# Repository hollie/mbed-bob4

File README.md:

mbed-bob4
=========

Basic breakout board for mbed (ethernet, USB, current sensor, GPIO)

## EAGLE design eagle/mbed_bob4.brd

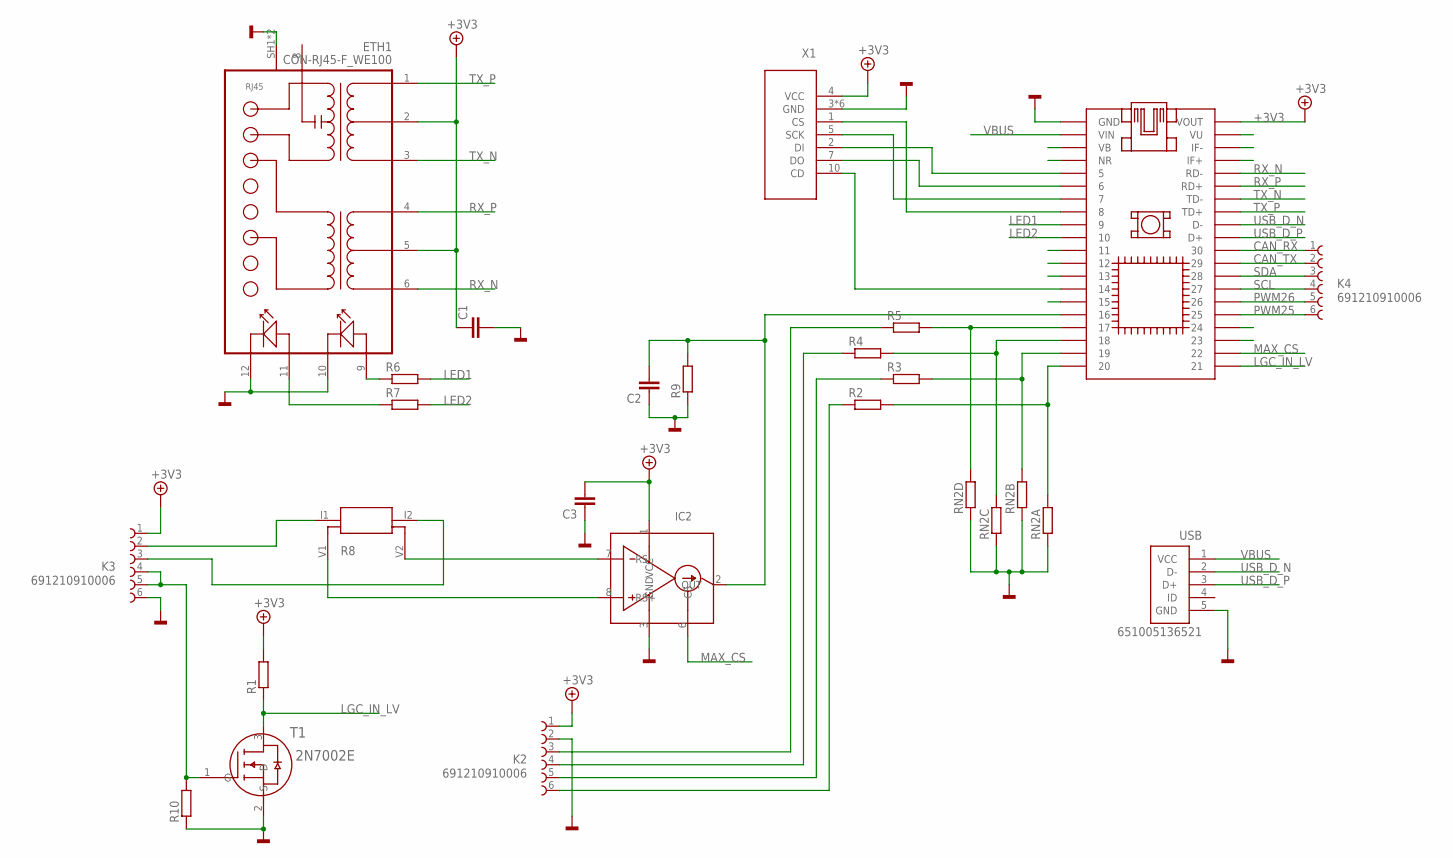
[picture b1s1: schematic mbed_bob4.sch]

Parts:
C1, C2, C3: C0805_RFLW; 0805_RFLW
ETH1: CON-RJ45-F_WE100; 74990111215A
IC1: MBED-SOCKET
IC2: MAX9934; UMAX8
K2, K3, K4: 691210910006
R1, R2, R3, R4, R5, R6, R7, R9, R10: R0805_RFLW; 0805_RFLW
R8: R_KELVIN; R_KELVIN_1206
RN2: RESISTOR_ARRAY_4TC164; RN_TC164
T1: 2N7002E; SOT23-3L
USB: 651005136521
X1: SDCARDSHORT; SD_SHORT

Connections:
+3V3: C1.P$3 (1), C3.P$4 (2), ETH1.2 (CTD), ETH1.5 (CRD), IC1.VOUT, IC1.VOUTA (VOUT), IC2.1 (VCC), K2.1, K3.1, R1.P$4 (2), X1.4 (VCC)
CAN_RX: IC1.30, IC1.30A (30), K4.1
CAN_TX: IC1.29, IC1.29A (29), K4.2
GND: C1.P$4 (2), C2.P$3 (1), C3.P$3 (1), ETH1.10 (YELLOW_CATHODE), ETH1.12 (GREEN_CATHODE), ETH1.SH1 (SHIELD), ETH1.SH2 (SHIELD), IC1.GND, IC1.GNDA (GND), IC2.3 (GND), K2.2, K3.6, R9.P$3 (1), R10.P$3 (1), RN2.1, RN2.2 (1), RN2.3 (1), RN2.4 (1), T1.2 (S), USB.5 (GND), X1.3 (GND), X1.6 (GND), X1.GND@1 (GND), X1.GND@2 (GND), X1.GND@3 (GND), X1.GND@4 (GND)
LED1: IC1.9, IC1.9A (9), R6.P$4 (2)
LED2: IC1.10, IC1.10A (10), R7.P$4 (2)
LGC_IN_LV: IC1.21, IC1.21A (21), R1.P$3 (1), T1.3 (D)
MAX_CS: IC1.22, IC1.22A (22), IC2.6 (CS)
unnamed: IC1.17, IC1.17A (17), R5.P$4 (2), RN2.5 (2)
unnamed: IC1.14, IC1.14A (14), X1.10 (CD)
unnamed: K2.6, R2.P$3 (1)
unnamed: IC1.20, IC1.20A (20), R2.P$4 (2), RN2.8 (2)
unnamed: IC1.19, IC1.19A (19), R3.P$4 (2), RN2.7 (2)
unnamed: IC1.18, IC1.18A (18), R4.P$4 (2), RN2.6 (2)
unnamed: K2.5, R3.P$3 (1)
unnamed: K2.4, R4.P$3 (1)
unnamed: K2.3, R5.P$3 (1)
unnamed: ETH1.11 (GREEN_ANODE), R7.P$3 (1)
unnamed: ETH1.9 (YELLOW_ANODE), R6.P$3 (1)
unnamed: K3.4, K3.5, R10.P$4 (2), T1.1 (G)
unnamed: IC1.7, IC1.7A (7), X1.5 (SCK)
unnamed: IC1.8, IC1.8A (8), X1.1 (CS)
unnamed: IC1.5, IC1.5A (5), X1.2 (DI)
unnamed: IC1.6, IC1.6A (6), X1.7 (DO)
unnamed: IC1.VB, IC1.VBA (VB)
unnamed: IC1.NR, IC1.NRA (NR)
unnamed: IC1.11, IC1.11A (11)
unnamed: IC1.12, IC1.12A (12)
unnamed: IC1.13, IC1.13A (13)
unnamed: IC1.15, IC1.15A (15)
unnamed: C2.P$4 (2), IC1.16, IC1.16A (16), IC2.2 (OUT), R9.P$4 (2)
unnamed: K3.2, R8.I1
unnamed: IC1.23, IC1.23A (23)
unnamed: IC1.24, IC1.24A (24)
unnamed: IC1.IF+, IC1.IF+A (IF+)
unnamed: IC1.IF-, IC1.IF-A (IF-)
unnamed: IC1.VU, IC1.VUA (VU)
unnamed: IC2.7 (RS-), R8.V2
unnamed: IC2.8 (RS+), R8.V1
unnamed: K3.3, R8.I2
PWM25: IC1.25, IC1.25A (25), K4.6
PWM26: IC1.26, IC1.26A (26), K4.5
RX_N: ETH1.6 (RD-), IC1.RD-, IC1.RD-A (RD-)
RX_P: ETH1.4 (RD+), IC1.RD+, IC1.RD+A (RD+)
SCL: IC1.27, IC1.27A (27), K4.4
SDA: IC1.28, IC1.28A (28), K4.3
TX_N: ETH1.3 (TD-), IC1.TD-, IC1.TD-A (TD-)
TX_P: ETH1.1 (TD+), IC1.TD+, IC1.TD+A (TD+)
USB_D_N: IC1.D-, IC1.D-A (D-), USB.2 (D-)
USB_D_P: IC1.D+, IC1.D+A (D+), USB.3 (D+)
VBUS: IC1.VIN, IC1.VINA (VIN), USB.1 (VCC)

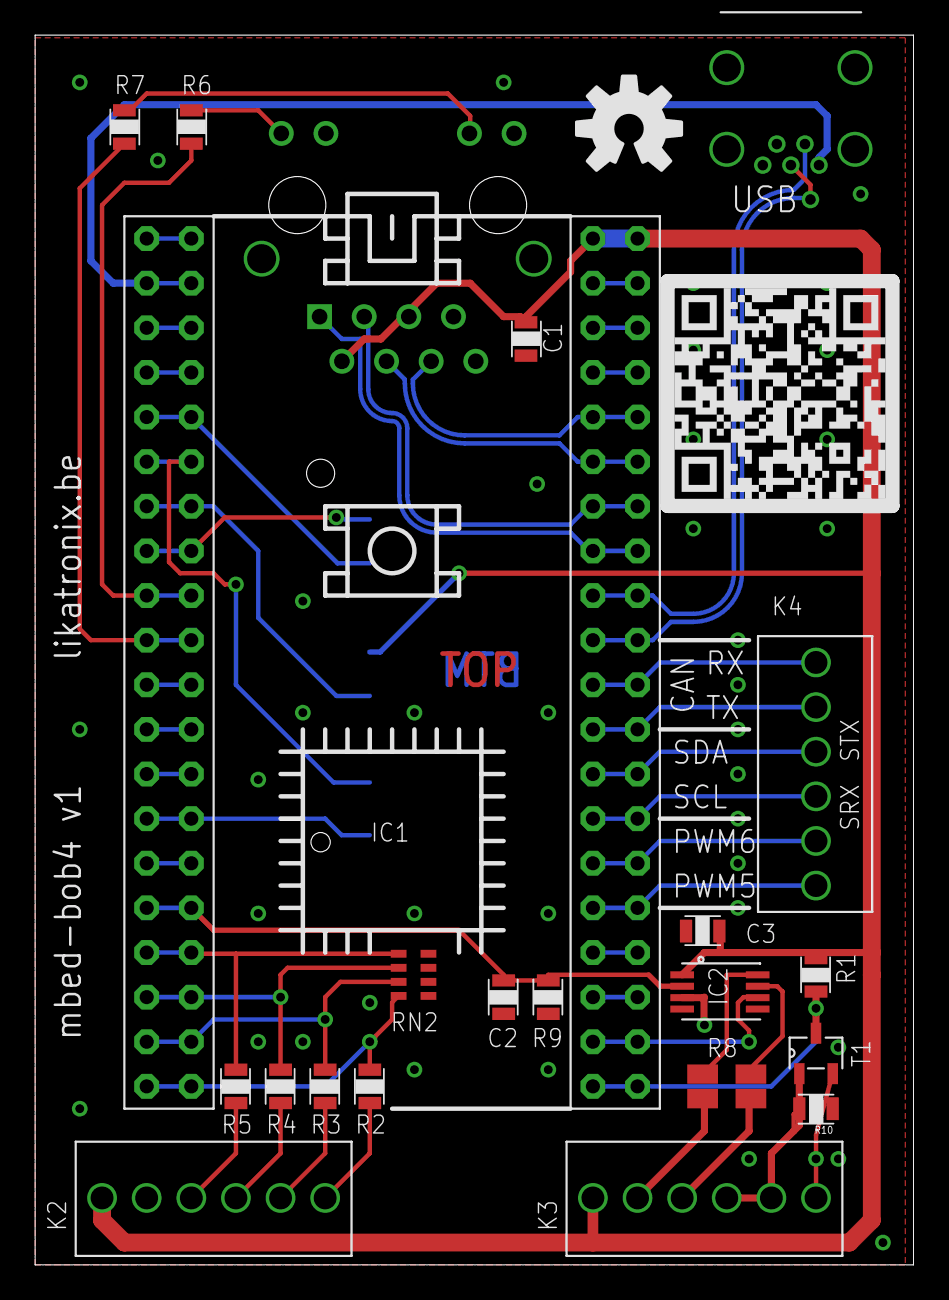
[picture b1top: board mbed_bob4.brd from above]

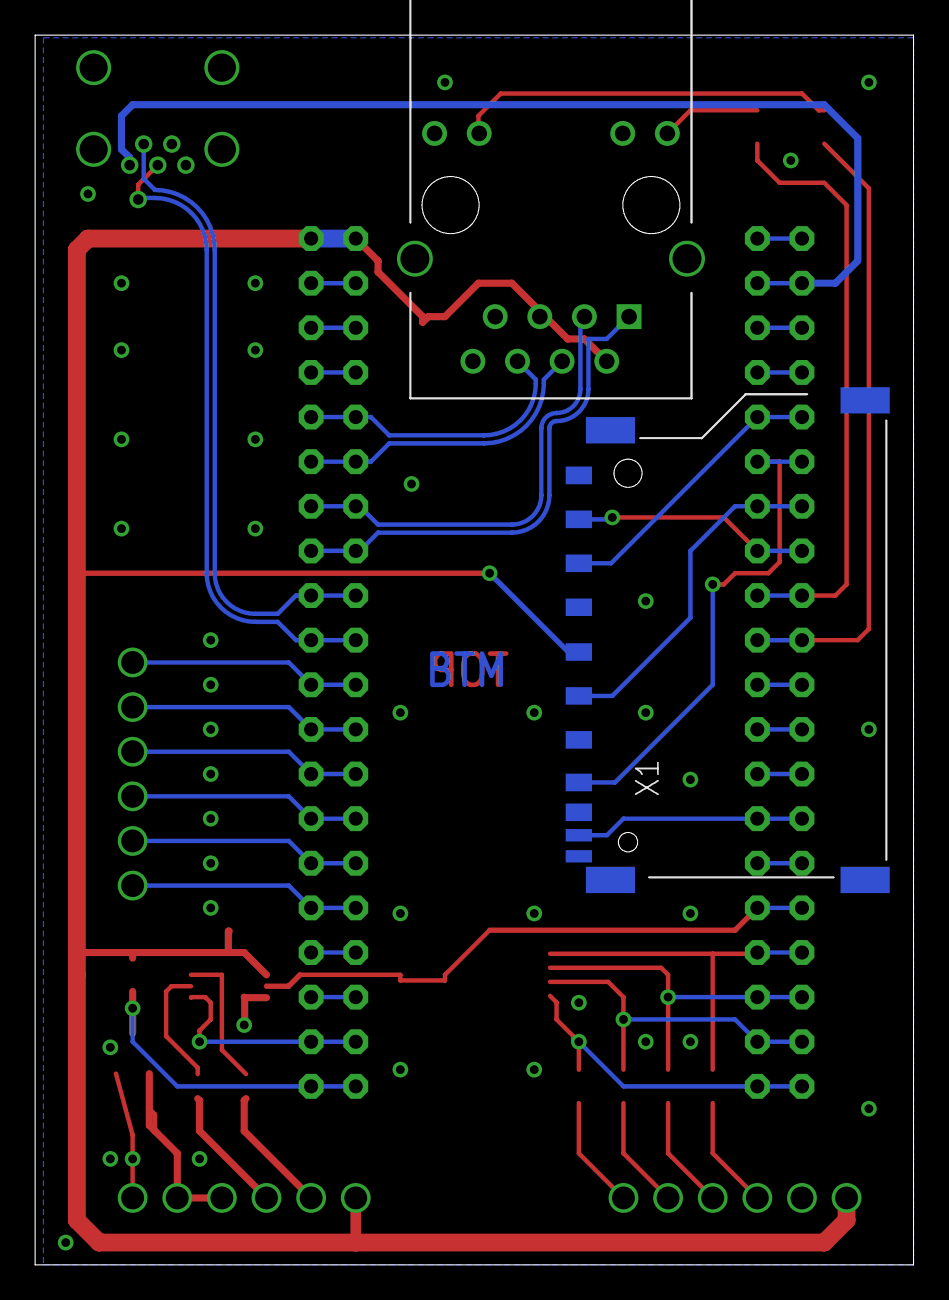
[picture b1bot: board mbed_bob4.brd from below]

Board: 2 copper layers, 50.0 x 70.0 mm, 23 parts (2 on the bottom side), 51 nets.

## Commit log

2013-05-11 Added first version of the BOB. Need to add current measurement hardware.
2013-05-13 First working version. To be cleaned up and checked before sending out for production.
2013-05-14 Further cleanup
2013-05-14 Final version before boardout.
2013-05-14 Added datasheet of current sense amplifier.
2013-05-14 Added decoupling resistor.
2013-05-15 Fixed OAR error.
2013-11-02 Updated eagle.epf
2013-11-02 Removed eagle.epf from project.

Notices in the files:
parts and their libraries:
Wuerth_Elektronik_eiCan_11_Communication: Copyright: Würth Elektronik
